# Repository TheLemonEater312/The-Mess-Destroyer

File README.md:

# The Mess Destroyer

### AI-Powered mess Detection System

## About the Project

The Mess Destroyer is a smart device designed to detect messy desks, shelves, and other surfaces using AI.

The goal is to help people keep their workspace organized by automatically identifying messy areas and sending notifications to their phone.

## How It Works

The planned system works in four steps:

1. A camera captures images of the place.
2. A Raspberry Pi Compute Module 5 processes the images using AI.
3. The software determines whether the workspace is messy or organized.
4. If mess is detected, the device sends a notification to the users phone.

## Hardware

The project uses or plans to use:

- Raspberry Pi Compute Module 5
- Raspberry Pi Camera Module 3 Wide
- Custom PCB designed in KiCad
- ESP32 for additional control and connectivity
- Waveshare UPS module
- Rechargeable batteries
- Small 5V cooling fan
- Electronic connectors and supporting components

## PCB Design

The custom PCB is being designed using KiCad.

The hardware design files and Bill of Materials will be available in this repository.

## Software

The planned software includes:

- Image capture
- AI-based mess detection
- Phone notifications
- Device configuration and monitoring

## Project Status

**In development**

## Project Goal

To create a compact, practical, and intelligent device that makes workspace organization easier through computer vision and automation.

## Images of the schematic and pcb

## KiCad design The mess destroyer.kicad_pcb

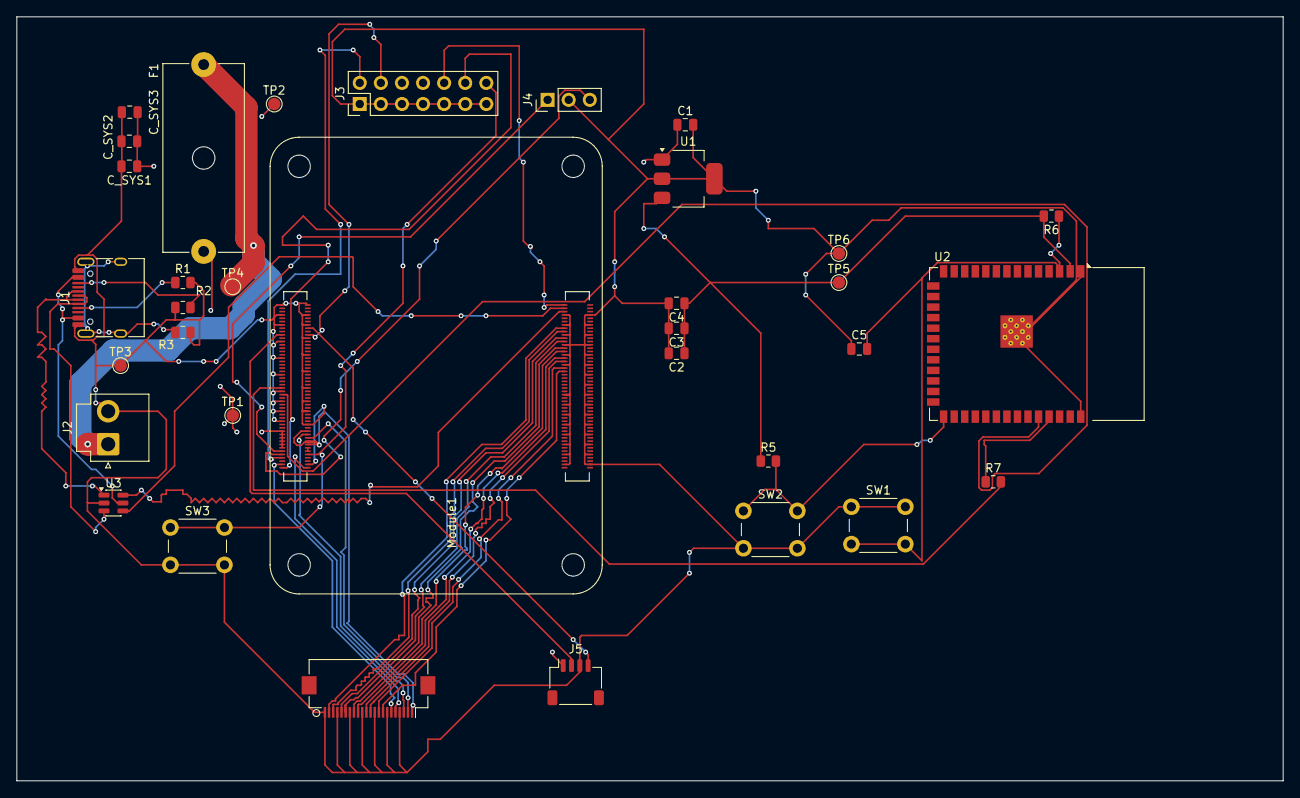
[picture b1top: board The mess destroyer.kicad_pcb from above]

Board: 4 copper layers, 152.5 x 92.0 mm, 34 parts (0 on the bottom side), 42 nets.

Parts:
C1, C2, C4: 10uF; C_0805_2012Metric
C3: 100nF; C_0805_2012Metric
C5: 1uF; C_0805_2012Metric
C_SYS1: 100uF; C_0805_2012Metric
C_SYS2: 10uF; C_0805_2012Metric
C_SYS3: 100nF; C_0805_2012Metric
F1: 5A; Fuseholder_Cylinder-5x20mm_Schurter_0031_8201_Horizontal_Op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
J1: USB_C_Receptacle_USB2.0_16P; USB_C_Receptacle_HRO_TYPE-C-31-M-12
J2: UPS_5V_INPUT; JST_VH_B2P-VH_1x02_P3.96mm_Vertical
J3: Conn_02x07_Odd_Even; PinHeader_2x07_P2.54mm_Vertical
J4: Conn_01x03; PinHeader_1x03_P2.54mm_Vertical
J5: FAN_5V_PWM; JST_SH_SM04B-SRSS-TB_1x04-1MP_P1.00mm_Horizontal
J9: Conn_01x22_Female; Hirose_FH12-22S-0.5SH_1x22-1MP_P0.50mm_Horizontal
Module1: ComputeModule5-CM5; Raspberry-Pi-5-Compute-Module
R1, R2: 5.1k; R_0805_2012Metric
R3: 0R; R_0805_2012Metric
R5, R6: 10k; R_0805_2012Metric
R7: 499R; R_0805_2012Metric
SW1: RESET; SW_PUSH_6mm
SW2: BOOT; SW_PUSH_6mm
SW3: Right angle Tact button; SW_PUSH_6mm
TP1, TP2, TP3, TP4, TP5, TP6: TestPoint; TestPoint_Pad_D1.5mm
U1: AP7361C-33E; SOT-223-3_TabPin2
U2: ESP32-S3-WROOM-1-N16R8; ESP32-S3-WROOM-1
U3: USBLC6-2SC6; SOT-23-6

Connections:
/CM5_GPIO ( Ethernet, GPIO, SDCARD)/+1.8v: Module1.88 (+1.8v_(Output)), Module1.90 (+1.8v_(Output))
/CM5_GPIO ( Ethernet, GPIO, SDCARD)/+3.3v: J9.22, Module1.78 (GPIO_VREF(1.8v/3.3v_Input)), Module1.84 (+3.3v_(Output)), Module1.86 (+3.3v_(Output))
/CM5_GPIO ( Ethernet, GPIO, SDCARD)/BT_nDis: J4.3, Module1.91 (BT_nDisable)
/CM5_GPIO ( Ethernet, GPIO, SDCARD)/CAM_GPIO0: J9.17, Module1.97 (CAM_GPIO0)
/CM5_GPIO ( Ethernet, GPIO, SDCARD)/CAM_GPIO1: J9.18, Module1.100 (CAM_GPIO1)
/CM5_GPIO ( Ethernet, GPIO, SDCARD)/EEPROM_nWP: J3.4, Module1.20 (EEPROM_nWP)
/CM5_GPIO ( Ethernet, GPIO, SDCARD)/PMIC_ENABLE: J3.12, Module1.99 (PMIC_ENABLE)
/CM5_GPIO ( Ethernet, GPIO, SDCARD)/PWR_BUT: J3.14, Module1.92 (PWR_BUT), SW3.1
/CM5_GPIO ( Ethernet, GPIO, SDCARD)/USBOTG: J3.10, Module1.101 (USB_OTG_ID)
/CM5_GPIO ( Ethernet, GPIO, SDCARD)/WL_nDis: J4.1, Module1.89 (WiFi_nDisable)
/CM5_GPIO ( Ethernet, GPIO, SDCARD)/nRPIBOOT: J3.2, Module1.93 (nRPIBOOT)
/CM5_HighSpeed/DPHY0_C_N: J9.8, Module1.127 (MIPI0_C_N)
/CM5_HighSpeed/DPHY0_C_P: J9.9, Module1.129 (MIPI0_C_P)
/CM5_HighSpeed/DPHY0_D0_N: J9.2, Module1.115 (MIPI0_D0_N)
/CM5_HighSpeed/DPHY0_D0_P: J9.3, Module1.117 (MIPI0_D0_P)
/CM5_HighSpeed/DPHY0_D1_N: J9.5, Module1.121 (MIPI0_D1_N)
/CM5_HighSpeed/DPHY0_D1_P: J9.6, Module1.123 (MIPI0_D1_P)
/CM5_HighSpeed/DPHY0_D2_N: J9.11, Module1.133 (MIPI0_D2_N)
/CM5_HighSpeed/DPHY0_D2_P: J9.12, Module1.135 (MIPI0_D2_P)
/CM5_HighSpeed/DPHY0_D3_N: J9.14, Module1.139 (MIPI0_D3_N)
/CM5_HighSpeed/DPHY0_D3_P: J9.15, Module1.141 (MIPI0_D3_P)
/CM5_HighSpeed/SCL0: J9.20, Module1.80 (SCL0)
/CM5_HighSpeed/SDA0: J9.21, Module1.82 (SDA0)
/ESP_3V3: C2.1, C3.1, C4.1, R5.1, R6.2, TP5.1 (1_1), U1.3 (VO), U2.2 (3V3)
/USB2_N: Module1.103 (USB2_N), U3.4 (I/O2)
/USB2_P: Module1.105 (USB2_P), U3.6 (I/O1)
/VIN_5V: F1.2, J2.1, TP4.1 (1_1)
ESP_TX_TO_PI: Module1.51 (GPIO15), R7.2
GND: C1.2, C2.2, C3.2, C4.2, C5.1, C_SYS1.2, C_SYS2.2, C_SYS3.2, J1.A1 (GND), J1.A12 (GND), J1.B1 (GND), J1.B12 (GND), J2.2, J3.1, J3.3, J3.5, J3.7, J3.9, J3.11, J3.13, J4.2, J5.3, J9.1, J9.4, J9.7, J9.10, J9.13, J9.16, J9.19, Module1.1 (GND), Module1.2 (GND), Module1.7 (GND), Module1.8 (GND), Module1.13 (GND), Module1.14 (GND), Module1.22 (GND), Module1.23 (GND), Module1.32 (GND), Module1.33 (GND), Module1.42 (GND), Module1.43 (GND), Module1.52 (GND), Module1.53 (GND), Module1.59 (GND), Module1.60 (GND), Module1.65 (GND), Module1.66 (GND), Module1.71 (GND), Module1.74 (GND), Module1.98 (GND), Module1.107 (GND), Module1.108 (GND), Module1.113 (GND), Module1.114 (GND), Module1.119 (GND), Module1.120 (GND), Module1.125 (GND), Module1.126 (GND), Module1.131 (GND), Module1.132 (GND), Module1.137 (GND), Module1.138 (GND), Module1.144 (GND), Module1.150 (GND), Module1.155 (GND), Module1.156 (GND), Module1.161 (GND), Module1.162 (GND), Module1.167 (GND), Module1.168 (GND), Module1.173 (GND), Module1.174 (GND), Module1.179 (GND), Module1.180 (GND), Module1.185 (GND), Module1.186 (GND), Module1.191 (GND), Module1.192 (GND), Module1.197 (GND), Module1.198 (GND), R1.2, R2.1, R3.2, SW1.1, SW2.2, SW3.2, TP3.1 (1_1), TP6.1 (1_1), U1.2 (GND), U2.1 (GND), U2.40 (GND), U2.41 (GND), U3.2 (GND)
unnamed: J1.A5 (CC1), R1.1
unnamed: J1.B5 (CC2), R2.2
unnamed: J1.A6 (D+), J1.B6 (D+), U3.1 (I/O1)
unnamed: J1.A7 (D-), J1.B7 (D-), U3.3 (I/O2)
unnamed: J1.SH (SHIELD), R3.1
unnamed: J5.2, Module1.19 (FAN_PWM)
unnamed: J5.4, Module1.16 (FAN_TACHO)
unnamed: C5.2, R6.1, SW1.2, U2.3 (EN)
unnamed: R5.2, SW2.1, U2.27 (IO0)
unnamed: R7.1, U2.37 (TXD0)
unnamed: J1.A4 (VBUS), J1.A9 (VBUS), J1.B4 (VBUS), J1.B9 (VBUS), U3.5 (VBUS)
PI_TX_TO_ESP: Module1.55 (GPIO14), U2.36 (RXD0)
SYS_5V: C1.1, C_SYS1.1, C_SYS2.1, C_SYS3.1, F1.1, J5.1, Module1.77 (+5v_(Input)), Module1.79 (+5v_(Input)), Module1.81 (+5v_(Input)), Module1.83 (+5v_(Input)), Module1.85 (+5v_(Input)), Module1.87 (+5v_(Input)), TP1.1 (1_1), TP2.1 (1_1), U1.1 (VI)
